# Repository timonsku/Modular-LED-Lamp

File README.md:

# Modular-LED-Lamp
<br />This work is licensed under a <a rel="license" href="http://creativecommons.org/licenses/by-sa/4.0/">Creative Commons Attribution-ShareAlike 4.0 International License</a>.

For more details see https://hackaday.io/project/20653-dirt-cheap-modular-led-lighting-system

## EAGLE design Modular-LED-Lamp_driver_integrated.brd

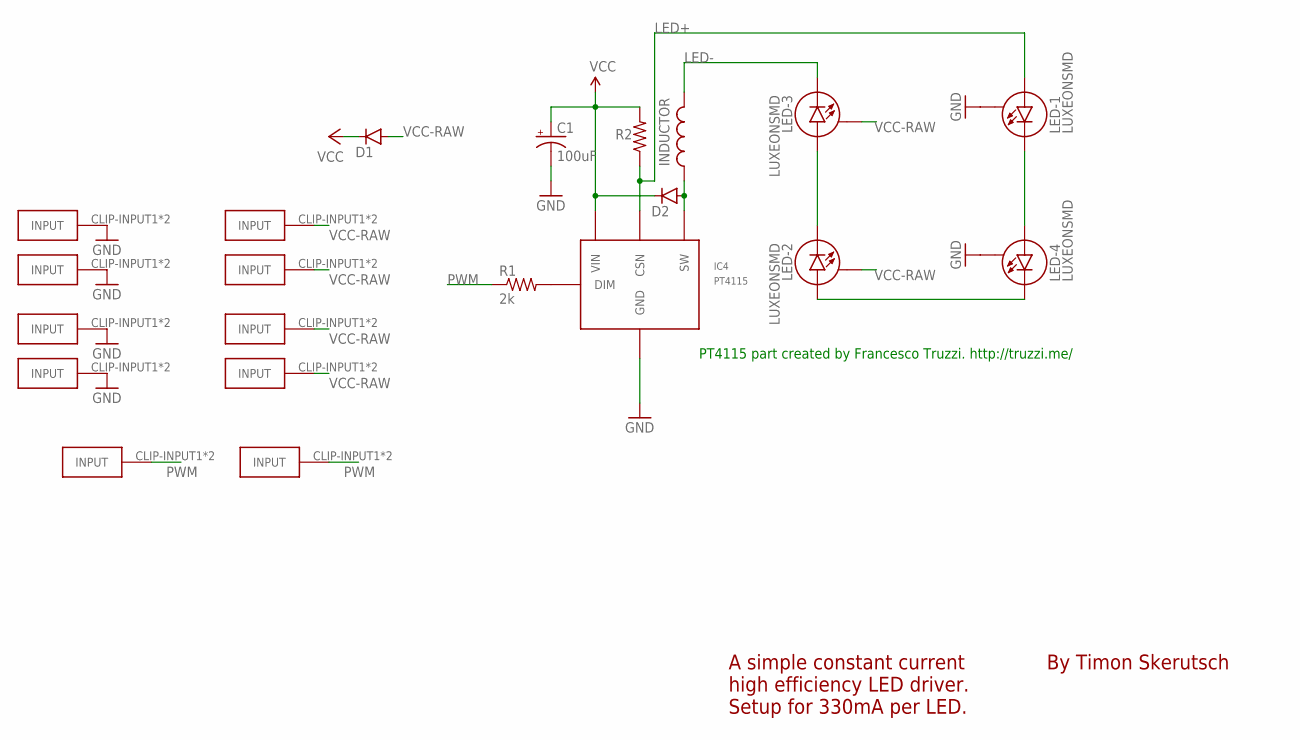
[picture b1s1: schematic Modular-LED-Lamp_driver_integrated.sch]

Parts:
C1: 100uF; PANASONIC_E
D1, D2: DIODESMA-KIT; SMA-DIODE-KIT
GND-CLIP, GND-CLIP1, GND-CLIP2, GND-CLIP3: FUSE-HOLDER-5X20MM
IC4: PT4115
INDUCTOR: MSS1260
LED-1, LED-2, LED-3, LED-4: LUXEONSMD; LUXEON
PWM-CLIP, PWM-CLIP1: FUSE-HOLDER-5X20MM
R1: 2k; 1206
R2: 0.3; 1206
VCC-CLIP, VCC-CLIP1, VCC-CLIP2, VCC-CLIP3: FUSE-HOLDER-5X20MM

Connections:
GND: C1.-, GND-CLIP.CLIP-INPUT1, GND-CLIP.CLIP-INPUT2, GND-CLIP1.CLIP-INPUT1, GND-CLIP1.CLIP-INPUT2, GND-CLIP2.CLIP-INPUT1, GND-CLIP2.CLIP-INPUT2, GND-CLIP3.CLIP-INPUT1, GND-CLIP3.CLIP-INPUT2, IC4.2 (GND), IC4.2A (GND), LED-1.S, LED-4.S
LED+: IC4.4 (CSN), LED-1.A, R2.1
LED-: INDUCTOR.P$1, LED-3.C
unnamed: D2.A, IC4.1 (SW), INDUCTOR.P$2
unnamed: LED-2.A, LED-4.C
unnamed: LED-2.C, LED-3.A
unnamed: LED-1.C, LED-4.A
unnamed: IC4.3 (DIM), R1.2
PWM: PWM-CLIP.CLIP-INPUT1, PWM-CLIP.CLIP-INPUT2, PWM-CLIP1.CLIP-INPUT1, PWM-CLIP1.CLIP-INPUT2, R1.1
VCC: C1.+, D1.C, D2.C, IC4.5 (VIN), R2.2
VCC-RAW: D1.A, LED-2.S, LED-3.S, VCC-CLIP.CLIP-INPUT1, VCC-CLIP.CLIP-INPUT2, VCC-CLIP1.CLIP-INPUT1, VCC-CLIP1.CLIP-INPUT2, VCC-CLIP2.CLIP-INPUT1, VCC-CLIP2.CLIP-INPUT2, VCC-CLIP3.CLIP-INPUT1, VCC-CLIP3.CLIP-INPUT2

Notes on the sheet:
PT4115 part created by Francesco Truzzi. http://truzzi.me/
By Timon Skerutsch
A simple constant current high efficiency LED driver. Setup for 330mA per LED.

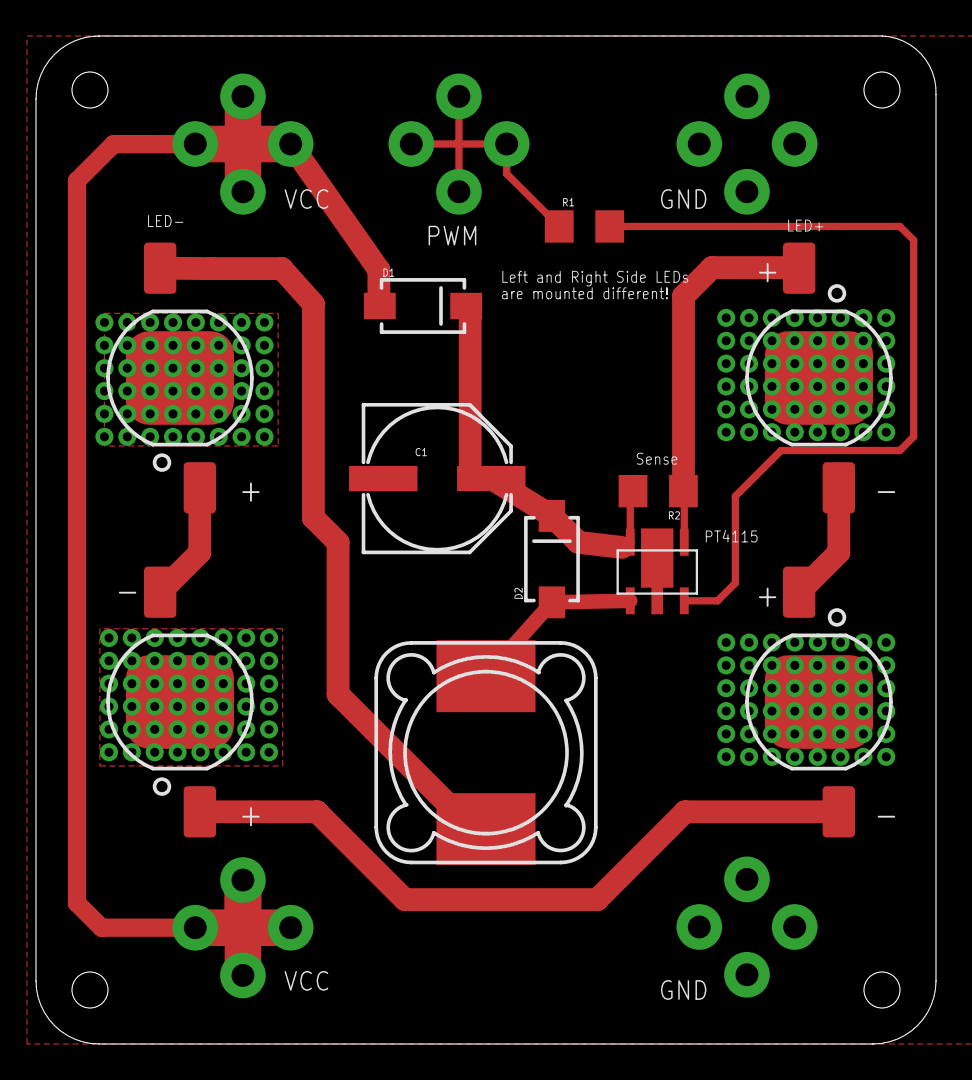
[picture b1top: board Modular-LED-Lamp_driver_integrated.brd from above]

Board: 2 copper layers, 50.0 x 56.0 mm, 21 parts (1 on the bottom side), 11 nets.

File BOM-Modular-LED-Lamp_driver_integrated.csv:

Qty,Value,Device,Package,Parts,Description,AliExpress Low Qty,AliExpress High Qty,Digikey
2,1A,DIODESMA-KIT,DO-214 (SMA) or SOD-123,"D1, D2",Diode,https://www.aliexpress.com/item/100pcs-sma-1N5819-SMD-IN5819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,https://www.aliexpress.com/item/Free-Shipping-1000PCS-1N5819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,https://www.digikey.de/product-detail/en/diodes-incorporated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
1,68uH,MSS1260 or similar,SMT D=7-10mm,INDUCTOR,SMT Power Inductor,https://www.aliexpress.com/item/25PCS-10-10-4MM-68UH-1-5A-SM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,,
1,PT4115,PT4115,PT4115,IC4,"30V, 1.2A Step-down Constant Current Driver",https://www.aliexpress.com/item/10pcs-PT4115B89E-SOT89-5-PT4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,https://www.aliexpress.com/item/200pcs-LOT-free-shipping-PT4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,
1,0.3,RESISTOR1206,1206,R2,Current Sense Resistor,https://www.aliexpress.com/item/1206-SMD-Resistor-1-0-3-ohm-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,https://www.aliexpress.com/item/1206-SMD-Resistor-1-0-3-ohm-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,
1,100uF 35 or 50v (rec.),CAP_POLE,PANASONIC_E (or D=6-8mm),C1,Capacitor Polarized,https://www.aliexpress.com/item/20pcs-lot-100uf-50V-SMD-Chip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,https://www.aliexpress.com/item/100pcs-lot-100uf-50V-SMD-Chi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,
1,2k,RESISTOR1206,1206,R1,Resistor,https://www.aliexpress.com/item/1206-2K-ohm-5-1-4W-Resistor-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,https://www.aliexpress.com/item/Free-shipping-full-reel-5-12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,
10,FUSE-HOLDER-5X20MM,FUSE-HOLDER-5X20MM,FUSE-HOLDER-5X20MM,"GND-CLIP, GND-CLIP1, GND-CLIP2, GND-CLIP3, PWM-CLIP, PWM-CLIP1, VCC-CLIP, VCC-CLIP1, VCC-CLIP2, VCC-CLIP3",5mm Fuse Holder,https://www.aliexpress.com/item/100pcs-lot-5x20-5-20mm-Fuse-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,https://www.aliexpress.com/item/500pcs-lot-5x20-mm-Fuse-Clip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,
4,LUXEONSMD,LUXEONSMD,LUXEON,"LED-1, LED-2, LED-3, LED-4",Luxeon LED (3W rec. More efficent than 1W variant),https://www.aliexpress.com/item/10pcs-Real-Full-Watt-CREE-1W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,https://www.aliexpress.com/item/Free-shipping-50PCS-1W-3w-Hi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,
„,„,„,„,„,Full Spectrum variant for plants,https://www.aliexpress.com/item/High-Power-LED-Chip-Deep-Red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,https://www.aliexpress.com/item/100pcs-LED-3W-400nm-840nm-Fu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,

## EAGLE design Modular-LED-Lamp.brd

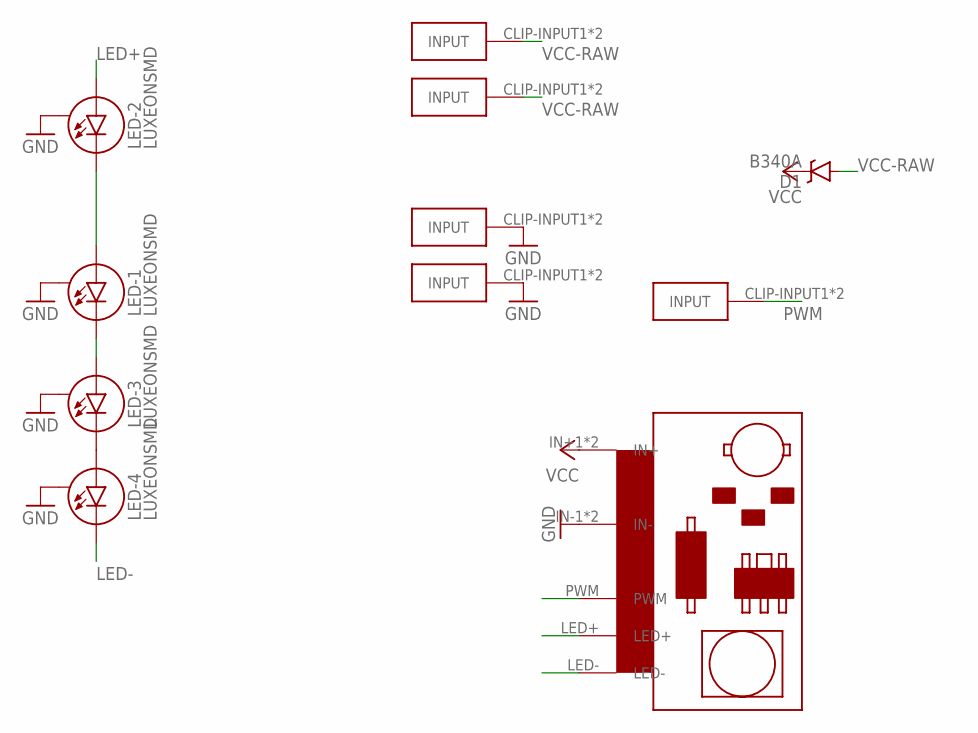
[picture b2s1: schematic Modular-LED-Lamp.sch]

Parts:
D1: B340A; SMA-DIODE
GND-CLIP, GND-CLIP2: GND; FUSE-HOLDER-5X20MM
LED-1, LED-2, LED-3, LED-4: LUXEONSMD; LUXEON
PWM-CLIP: FUSE-HOLDER-5X20MM
U$1: PT4115-MODULE
VCC-CLIP, VCC-CLIP2: FUSE-HOLDER-5X20MM

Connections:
GND: GND-CLIP.CLIP-INPUT1, GND-CLIP.CLIP-INPUT2, GND-CLIP2.CLIP-INPUT1, GND-CLIP2.CLIP-INPUT2, LED-1.S, LED-2.S, LED-3.S, LED-4.S, U$1.IN-1 (IN-), U$1.IN-2 (IN-)
LED+: LED-2.A, U$1.LED+
LED-: LED-4.C, U$1.LED-
unnamed: LED-1.C, LED-3.A
unnamed: LED-3.C, LED-4.A
unnamed: LED-1.A, LED-2.C
PWM: PWM-CLIP.CLIP-INPUT1, PWM-CLIP.CLIP-INPUT2, U$1.PWM
VCC: D1.C, U$1.IN+1 (IN+), U$1.IN+2 (IN+)
VCC-RAW: D1.A, VCC-CLIP.CLIP-INPUT1, VCC-CLIP.CLIP-INPUT2, VCC-CLIP2.CLIP-INPUT1, VCC-CLIP2.CLIP-INPUT2

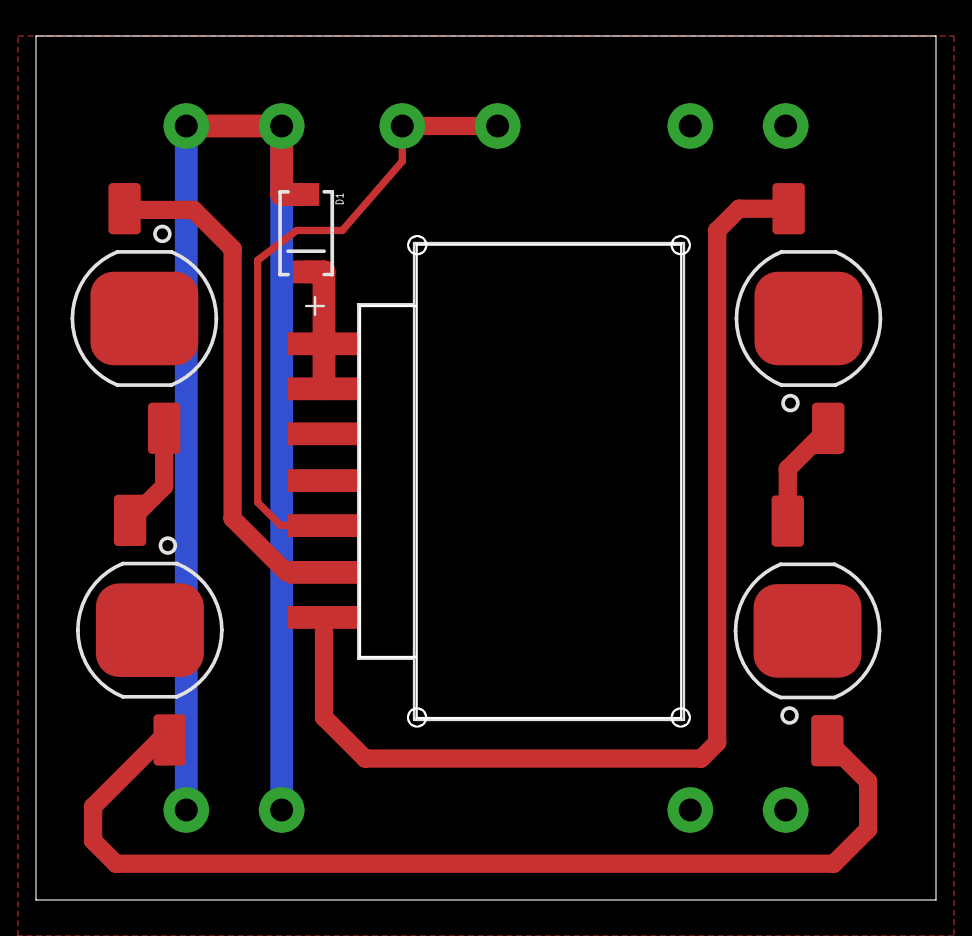
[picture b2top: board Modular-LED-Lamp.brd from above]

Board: 2 copper layers, 49.0 x 47.0 mm, 11 parts (0 on the bottom side), 9 nets.

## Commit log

2017-04-16 changed outline to be bigger to disspate more heat, added footprint for 90° turned fuse holders, rounded edges
2017-05-01 updated integrated driver module to be 1W instead of 3W
2017-05-01 updated gitignore for gerber related files
2017-05-01 applied gitignore changes to existing files
2017-05-19 fixed issued with PWM rod causing short circuit when two boards are mounted with one being reversed. Added PDF for schematic and board.
2017-05-20 added PDFs
2017-05-25 Added BOM, updated schematic and board for integrated variant
2017-09-15 Changed license to CC-BY-SA

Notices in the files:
parts and their libraries:
SparkFun-LED: Licensing: Creative Commons ShareAlike 4.0 International - https://creativecommons.org/licenses/by-sa/4.0
